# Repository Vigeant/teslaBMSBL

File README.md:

# teslaBMSBL

## Hardware

see eagle files to build the board hosting the teensy 3.2.

## dependencies

- TeensyView libs
  - <https://github.com/sparkfun/SparkFun_TeensyView_Arduino_Library/tree/master/examples>
- Snooze for lower power consumption
  - <https://github.com/duff2013/Snooze>

## Error codes on teensyView

| code | definition |
|:----:|------------|
| A | Modules Fault Loop |
| B | Battery Monitor Fault |
| C | BMS Serial communication Fault |
| D | BMS Cell Over Voltage Fault |
| E | BMS Cell Under Voltage Fault |
| F | BMS Over Temperature Fault |
| G | BMS Under Temperature Fault |
| H | BMS 12V Battery Over Voltage Fault |
| I | BMS 12V Battery Under Voltage Fault |
| J | BMS Water Sensor 1 Fault |
| K | BMS Water Sensor 2 Fault |
| L | Incorrect modules count |

## Connection to USB serial console

Serial Line: COMX (X typically = 7)
Speed: 115200

## controller state machine

<!-- [State machine](https://online.visual-paradigm.com/w/pmcoivfe/diagrams.jsp#diagram:proj=0&id=3) -->

```mermaid
    stateDiagram-v2

    state "INIT

    outL_12V_bat_chrg_buffer = 1;
    outpwm_pump_buffer = 0;
    outL_evcc_on_buffer = 1;
    outH_fault_buffer = 0;" as INIT

    state "STANDBY

    balanceCells();
    outL_evcc_on_buffer = HIGH;
    outH_fault_buffer = chargerInhibit;
    outL_12V_bat_chrg_buffer = !dc2dcON_H;
    outpwm_pump_buffer = 0;" as STANDBY

    state "RUN

    outL_evcc_on_buffer = LOW;
    outH_fault_buffer = powerLimiter;
    outL_12V_bat_chrg_buffer = LOW;
    outpwm_pump_buffer = YES" as RUN

    state "PRE_CHARGE

    balanceCells();
    outL_evcc_on_buffer = LOW;
    outH_fault_buffer = chargerInhibit;
    outL_12V_bat_chrg_buffer = !dc2dcON_H;
    outpwm_pump_buffer = 0;
    msgStatusIns.bBMSStatusFlags = 0;" as PRE_CHARGE

    state "CHARGING

    balanceCells();
    outL_evcc_on_buffer = LOW;
    outH_fault_buffer = chargerInhibit;
    outL_12V_bat_chrg_buffer = LOW;
    outpwm_pump_buffer = YES;
    msgStatusIns.bBMSStatusFlags = 0;" as CHARGING

    state "TOP_BALANCING

    balanceCells();
    msgStatusIns.bBMSStatusFlags |= BMS_STATUS_CELL_BVC_FLAG;
    outL_evcc_on_buffer = LOW;
    outH_fault_buffer = chargerInhibit;
    outL_12V_bat_chrg_buffer = HIGH;
    outpwm_pump_buffer = YES;
    msgStatusIns.bBMSStatusFlags = BMS_STATUS_CELL_BVC_FLAG;" as TOP_BALANCING

    state "POST_CHARGE

    balanceCells();
    outL_evcc_on_buffer = HIGH;
    outH_fault_buffer = HIGH;
    outL_12V_bat_chrg_buffer = HIGH;
    outpwm_pump_buffer = YES;
    msgStatusIns.bBMSStatusFlags = BMS_STATUS_CELL_HVC_FLAG;" as POST_CHARGE

    [*] --> INIT

    INIT --> STANDBY

    STANDBY --> RUN : INH_RUN == HIGH
    STANDBY --> PRE_CHARGE : getHighCellVolt < charger_cycle_v_setpoint && \ngetHighCellVolt < max_charge_v_setpoint && \nticks >= standbyTicks
    STANDBY --> CHARGING : INH_CHARGING == HIGH

    PRE_CHARGE --> STANDBY : INL_EVSE_DISC == LOW
    PRE_CHARGE --> CHARGING :INH_CHARGING == HIGH
    PRE_CHARGE --> STANDBY : ticks > 100

    CHARGING --> POST_CHARGE : ticks >= 5 && \nINL_EVSE_DISC == LOW || \nINH_CHARGING == LOW
    CHARGING --> TOP_BALANCING : getHighCellVolt >= top_balance_v_setpoint

    TOP_BALANCING --> POST_CHARGE : ticks >= 5 && \nINL_EVSE_DISC == LOW || \nINH_CHARGING == LOW

    POST_CHARGE --> STANDBY : ticks >= 50 && \nINH_CHARGING == LOW

    RUN --> STANDBY : INH_RUN == LOW

```

## todo

- [X] none

## particularities

Due to the 5s deepsleep mode in standby, it is hard to connect the serial console. To make it easier, either connect within 10 minutes of a reset or place the bms in run mode and connect.
Due to the deepsleep mode, it is impossible to simply reprogram the teensy following the first sleep. To facilitate reprogramming, the board will not sleep for 10 minutes following a reset.
The teensyview cannot be shut down as it is connected straight to the VDD pins.

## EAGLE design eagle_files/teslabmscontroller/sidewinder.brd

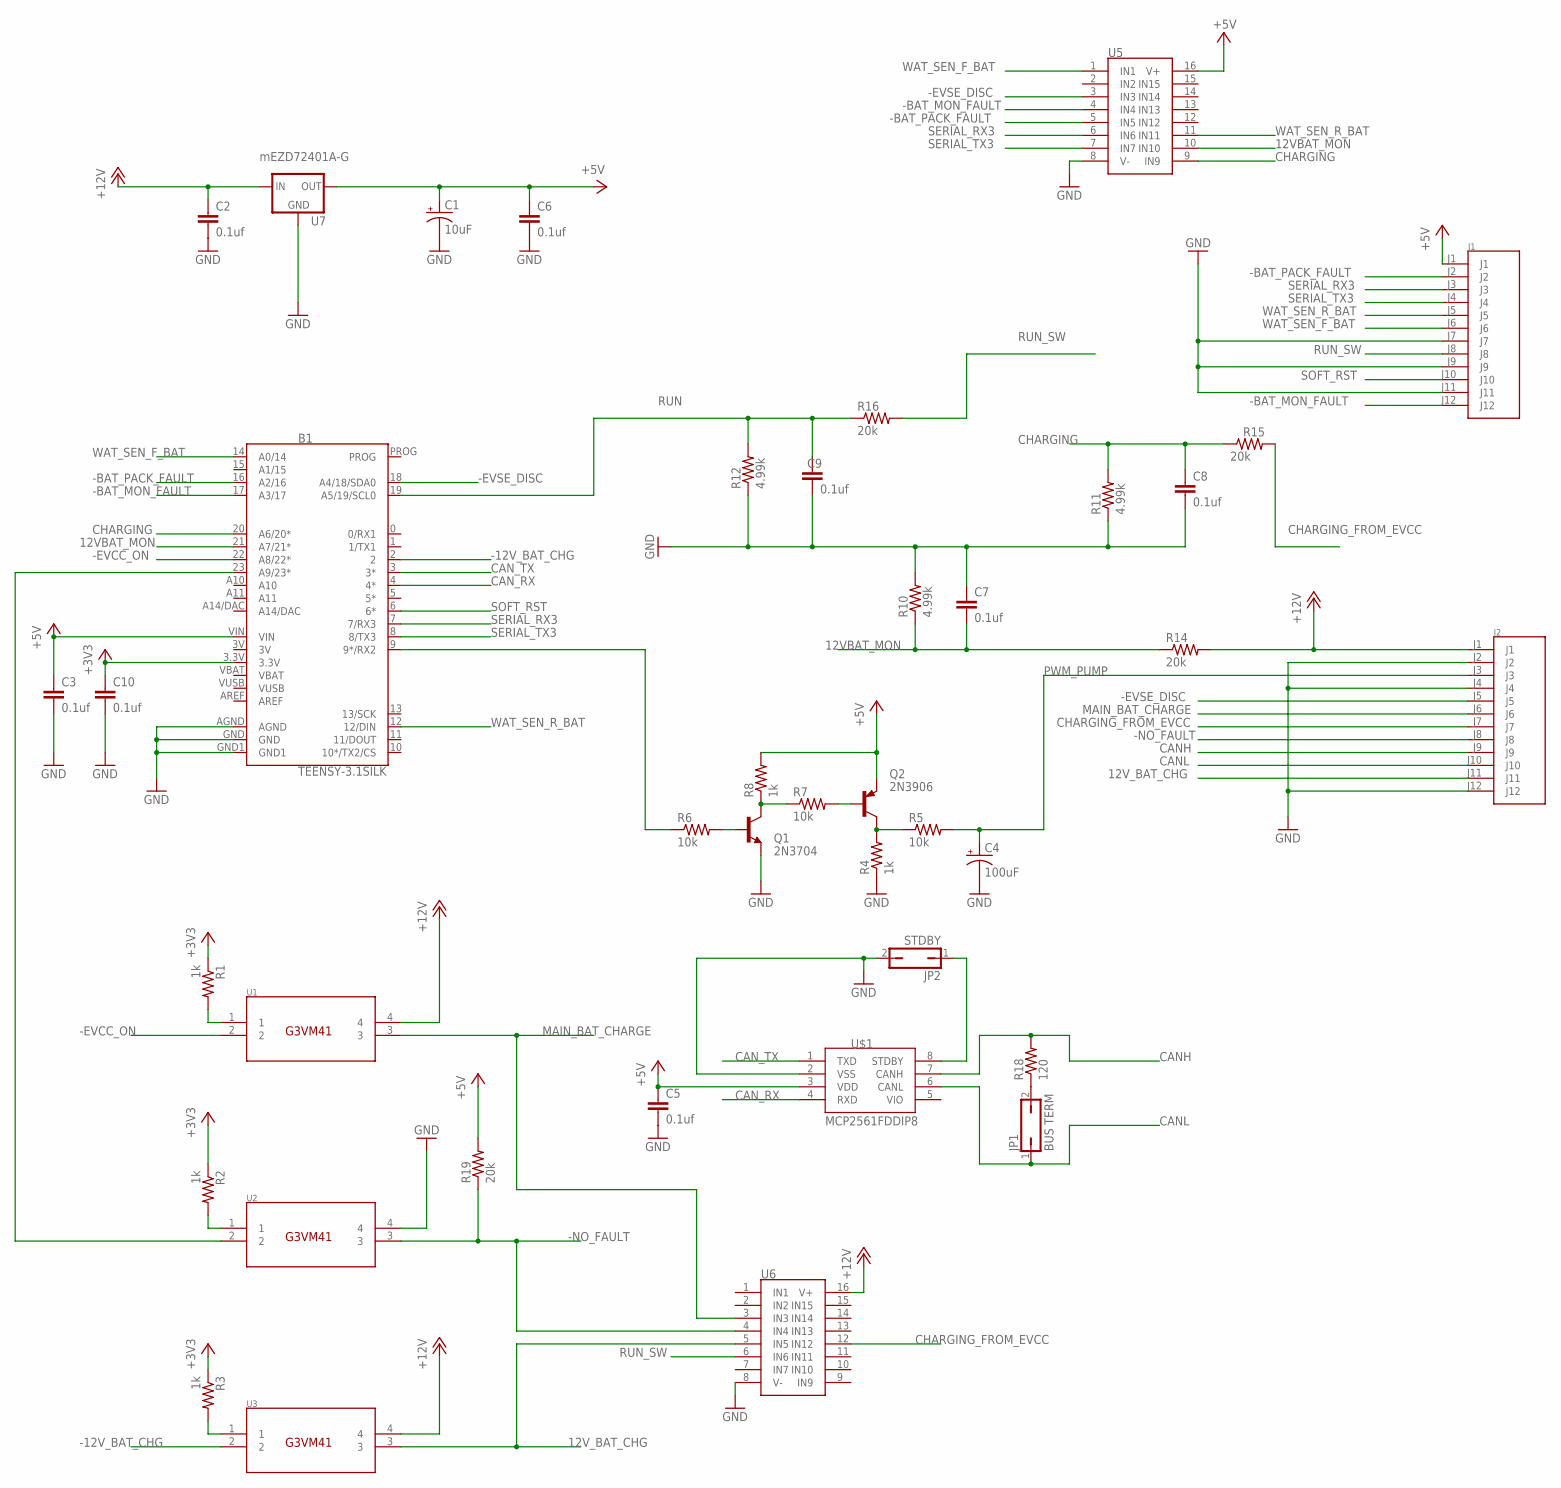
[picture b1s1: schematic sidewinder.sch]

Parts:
B1: TEENSY-3.1SILK; TEENSY-3.1
C1: 10uF; CPOL-RADIAL-2.5MM-5MM
C2, C3, C5, C6, C7, C8, C9, C10: 0.1uf; C2.5-2
C4: 100uF; CPOL-RADIAL-2.5MM-6.5MM
J1, J2: TERMINAL12
JP1: BUS TERM; JP1
JP2: STDBY; JP1
Q1: 2N3704; TO92
Q2: 2N3906; TO92
R1, R2, R3, R4, R8: 1k; 0207/10
R5, R6, R7: 10k; 0207/10
R10, R11, R12: 4.99k; 0207/10
R14, R15, R16, R19: 20k; 0207/10
R18: 120; 0207/10
U1, U2, U3: G3VM41
U5, U6: SP720APP; DIP16
U7: mEZD72401A-G; TO220-IGO
U$1: MCP2561FDDIP8; DIP787W45P254L949H533Q8B

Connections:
3V: B1.3V
12VBAT_MON: B1.21 (A7/21*), C7.2, R10.1, R14.1, U5.10 (IN10)
12V_BAT_CHG: J2.J11, U3.3, U6.5 (IN5)
+3V3: B1.3.3V, C10.1, R1.1, R2.1, R3.1
+5V: B1.VIN, C1.1 (+), C3.1, C5.1, C6.1, J1.J1, Q2.3 (E), R8.2, R19.2, U5.16 (V+), U7.OUT, U$1.3 (VDD)
+12V: C2.1, J2.J1, R14.2, U1.4, U3.4, U6.16 (V+), U7.IN
-12V_BAT_CHG: B1.2, U3.2
-BAT_MON_FAULT: B1.17 (A3/17), J1.J12, U5.4 (IN4)
-BAT_PACK_FAULT: B1.16 (A2/16), J1.J2, U5.5 (IN5)
-EVCC_ON: B1.22 (A8/22*), U1.2
-EVSE_DISC: B1.18 (A4/18/SDA0), J2.J5, U5.3 (IN3)
-NO_FAULT: J2.J8, R19.1, U2.3, U6.4 (IN4)
CANH: J2.J9, R18.2, U$1.7 (CANH)
CANL: J2.J10, JP1.1, U$1.6 (CANL)
CAN_RX: B1.4 (4*), U$1.4 (RXD)
CAN_TX: B1.3 (3*), U$1.1 (TXD)
CHARGING: B1.20 (A6/20*), C8.1, R11.2, R15.1, U5.9 (IN9)
CHARGING_FROM_EVCC: J2.J7, R15.2, U6.12 (IN12)
GND: B1.AGND, B1.GND, B1.GND1, C1.2 (-), C2.2, C3.2, C4.2 (-), C5.2, C6.2, C7.1, C8.2, C9.2, C10.2, J1.J7, J1.J9, J1.J11, J2.J2, J2.J4, J2.J12, JP2.2, Q1.3 (E), R4.1, R10.2, R11.1, R12.1, U2.4, U5.8 (V-), U6.8 (V-), U7.GND, U$1.2 (VSS)
MAIN_BAT_CHARGE: J2.J6, U1.3, U6.3 (IN3)
unnamed: B1.23 (A9/23*), U2.2
unnamed: B1.9 (9*/RX2), R6.1
unnamed: Q1.1 (B), R6.2
unnamed: Q1.2 (C), R7.1, R8.1
unnamed: Q2.2 (B), R7.2
unnamed: R1.2, U1.1
unnamed: R2.2, U2.1
unnamed: R3.2, U3.1
unnamed: Q2.1 (C), R4.2, R5.1
unnamed: JP2.1, U$1.8 (STDBY)
unnamed: JP1.2, R18.1
PWM_PUMP: C4.1 (+), J2.J3, R5.2
RUN: B1.19 (A5/19/SCL0), C9.1, R12.2, R16.1
RUN_SW: J1.J8, R16.2, U6.6 (IN6)
SERIAL_RX3: B1.7 (7/RX3), J1.J3, U5.6 (IN6)
SERIAL_TX3: B1.8 (8/TX3), J1.J4, U5.7 (IN7)
SOFT_RST: B1.6 (6*), J1.J10
VBAT: B1.VBAT
VUSB: B1.VUSB
WAT_SEN_F_BAT: B1.14 (A0/14), J1.J6, U5.1 (IN1)
WAT_SEN_R_BAT: B1.12 (12/DIN), J1.J5, U5.11 (IN11)

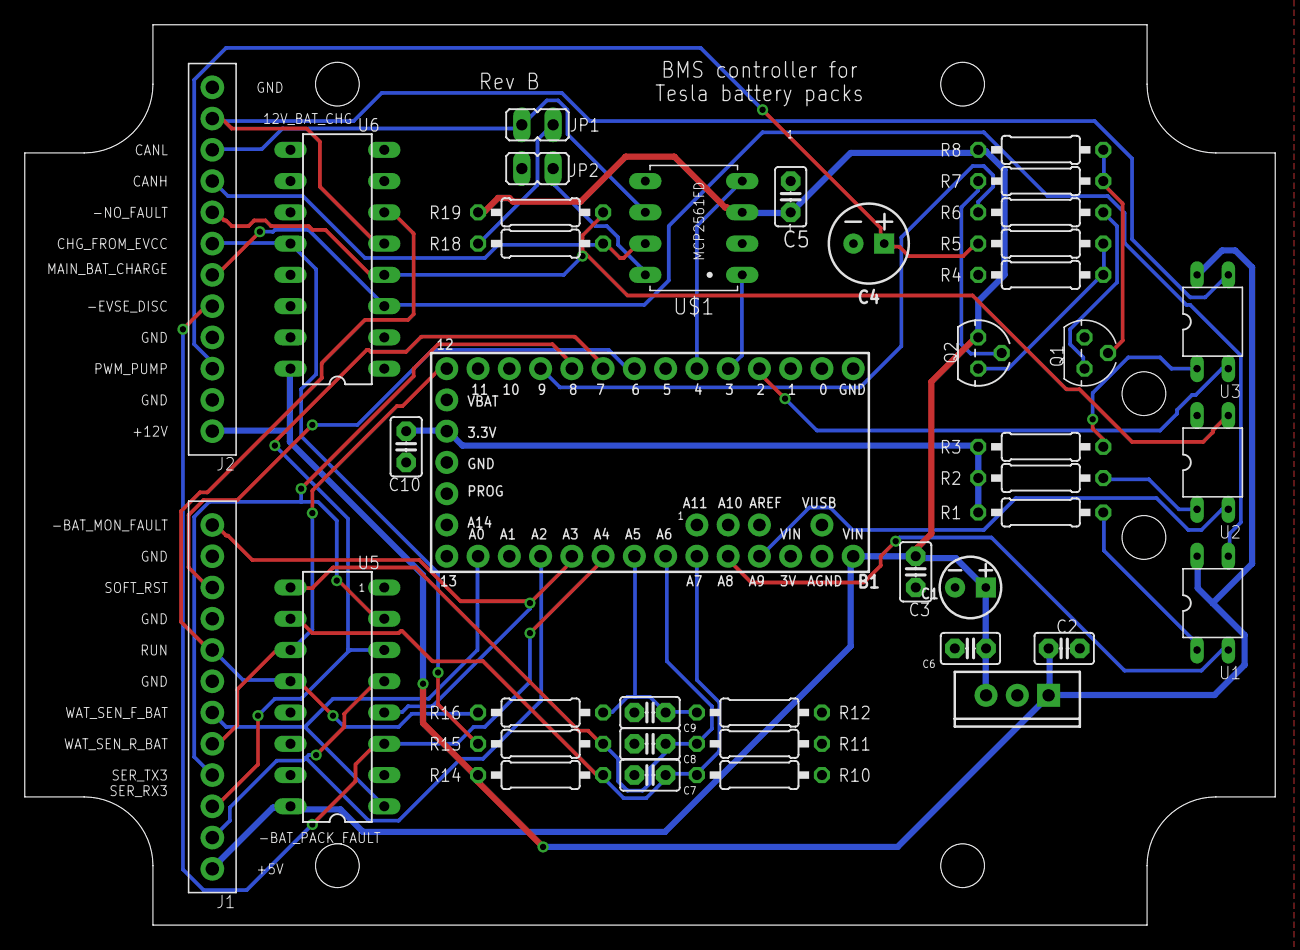
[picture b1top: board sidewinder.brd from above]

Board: 2 copper layers, 101.6 x 73.2 mm, 40 parts (0 on the bottom side), 38 nets.

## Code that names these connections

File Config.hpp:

#pragma once

#include <Arduino.h>
#include <EEPROM.h>
#include <list>

//enable testing mode that simply cycles through all states instead of triggers
//#define STATECYCLING 1
#define TESTING_MODE 0

///////////////////////////////////
// Teensy pin configuration      //
///////////////////////////////////
//side 1
//#define SERIAL1_RX          0
//#define SERIAL1_TX          1
#define OUTL_12V_BAT_CHRG 2  //Drive low to turn the DC2DC converter to charge the 12V battery
#define CAN_TX 3
#define CAN_RX 4
#define OLED_PIN_DC 5
#define INL_SOFT_RST 6  // soft reset of the teensy
#define SERIAL3_RX 7    // from Tesla BMS
#define SERIAL3_TX 8    // to Tesla BMS
#define OUTPWM_PUMP 9   // PWM to coolant pump
#define OLED_PIN_CS 10
#define OLED_PIN_MOSI 11
#define INL_WATER_SENS1 12  // battery enclosure water sensor 1

//side 2
#define OLED_PIN_SCK 13     //LED
#define INL_WATER_SENS2 14  // battery enclosure water sensor 2
#define OLED_PIN_RESET 15
#define INL_BAT_PACK_FAULT 16  //Tesla Battery pack fault.
#define INL_BAT_MON_FAULT 17   //Battery Monitor Fault.
#define INL_EVSE_DISC 18       //Electric Vehicle Supply Equipment Disconnected (from EVCC). (set Out2)
#define INH_RUN 19             //RUN signal from power relay with voltage divider from 12V to 3.3V.
#define INH_CHARGING 20        //CHARGING signal from EVCC. (Set Out1 to charging switched 12V)
#define INA_12V_BAT A7         //PIN21 12v battery monitor. Analog input with 12V to 3.3V voltage divider.
#define OUTL_EVCC_ON 22        //drive low to power on EVCC. Cycling this signal will force a new charge cycle.
#define OUTH_FAULT 23          //drive low to signal no fault to EVCC. Required for EVCC to charge.

//top side
//short P and G to reset board into program mode using push button

//Set to the proper port for your USB connection - SerialUSB on Due (Native) or Serial for Due (Programming) or Teensy
#define SERIALCONSOLE Serial

/*
   State machine
*/
// Loop periods for the state machine of the controller
#define LOOP_PERIOD_ACTIVE_MS 200

#define EEPROM_VERSION 6

#define CPU_RESTART_ADDR (uint32_t *)0xE000ED0C
#define CPU_RESTART_VAL 0x5FA0004
#define CPU_RESTART (*CPU_RESTART_ADDR = CPU_RESTART_VAL);

class Param {
public:
  Param(const char* paramName, bool editable, const char* description)
    : paramName(paramName),
      editable(editable),
      description(description) {
    ;
  }
  const char* paramName;
  virtual void prettyPrint();
  virtual int32_t setVal(const char* valStr);
  virtual uint16_t getSize();
  virtual void resetDefault();
  virtual uint32_t saveToEEPROM(uint32_t address);
  virtual uint32_t loadFromEEPROM(uint32_t address);
protected:
  bool editable = true;
  const char* description;
};

template<class C> class ParamImpl : public Param {
public:
  ParamImpl(const char* paramName, bool editable, C value, C valueDefault, C valueMin, C valueMax, const char* description)
    : Param(paramName, editable, description),
      value(value),
      valueDefault(valueDefault),
      valueMin(valueMin),
      valueMax(valueMax) {
    ;
  }

  void prettyPrint();
  int32_t setVal(const char*);

  C getVal() {
    return value;
  }

  void resetDefault() {
    value = valueDefault;
  }

  uint16_t getSize();
  bool valueMatchDefault() {
    return (value == valueDefault);
  }

  uint32_t saveToEEPROM(uint32_t address) {
    EEPROM.put(address, value);
    return sizeof(C);
  }

  uint32_t loadFromEEPROM(uint32_t address) {
    EEPROM.get(address, value);
    return sizeof(C);
  }

private:
  C value;
  C valueDefault;
  C valueMin;
  C valueMax;
};

class Settings {
public:
  void printSettings();
  Settings();
  Param* getParam(const char* name);
  uint16_t size();
  void reloadDefaultSettings();
  void saveAllSettingsToEEPROM(uint32_t address);
  void loadAllSettingsFromEEPROM(uint32_t address);

  ParamImpl<uint32_t> magic_bytes;
  ParamImpl<uint32_t> eeprom_version;
  ParamImpl<uint32_t> canbus_speed;
  ParamImpl<uint32_t> canbus_to_EVCC;
  ParamImpl<float> over_v_setpoint;
  ParamImpl<float> under_v_setpoint;
  ParamImpl<float> max_charge_v_setpoint;
  ParamImpl<float> charger_cycle_v_setpoint;
  ParamImpl<float> top_balance_v_setpoint;
  ParamImpl<float> warn_cell_v_offset;
  ParamImpl<float> floor_duty_coolant_pump;
  ParamImpl<float> cooling_lowt_setpoint;
  ParamImpl<float> cooling_hight_setpoint;
  ParamImpl<float> over_t_setpoint;
  ParamImpl<float> under_t_setpoint;
  ParamImpl<float> warn_t_offset;
  ParamImpl<float> precision_balance_v_setpoint;
  ParamImpl<float> precision_balance_cell_v_offset;
  ParamImpl<float> rough_balance_v_setpoint;
  ParamImpl<float> rough_balance_cell_v_offset;
  ParamImpl<float> dc2dc_cycle_v_setpoint;
  ParamImpl<uint32_t> dc2dc_cycle_time_s;
  ParamImpl<float> bat12v_over_v_setpoint;
  ParamImpl<float> bat12v_under_v_setpoint;
  ParamImpl<float> bat12v_scaling_divisor;
  ParamImpl<uint32_t> fault_debounce_count;
  ParamImpl<uint32_t> module_count;
  ParamImpl<uint32_t> oled_cycle_time;
  ParamImpl<uint32_t> time_before_first_sleep;

private:
  std::list<Param*> parameters;
};

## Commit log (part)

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2019-03-20 initial push
    Transitioned to the big loop design with a schedule.
2019-03-21 adding doxygen
2019-03-22 generated doxygen documentation
2019-03-22 added print summaries to the console
2019-03-22 tweaked the init state
2019-03-22 added colant pump pwm
2019-03-23 updated readme todo
2019-03-25 worked on state machine
2019-03-25 finished state machine
2019-03-25 cleaned config.h
2019-03-27 completed battery summary
2019-03-27 optimized controller
2019-03-27 fixes
2019-03-27 improved pack summary
2019-03-27 added 12V bat stats
2019-03-27 fixed bug in controller
2019-04-28 added hysterisy for faults
    after witnessing some fault glitches, we added hysteresy that requires the fault to be present for three ticks for it to be considered.
    Fixed coolant pump scaling issue,
    Added some more balancing functionality. More thaught required.
2019-05-04 safer behavior
    This will keep the dc2dc on while it waits for the charger to turn on.
2019-05-05 fixed console sometimes dropping a character
2019-05-06 added controller fault printout
2019-05-17 showing current vdmax on oled
2019-05-26 implemented the two water sensor lines
2019-05-26 fixed init of water sensor pins
2019-07-06 adjusted 12v divisor
2019-07-07 ADJUSTED SCALING
2019-07-09 major state machine change
    Modified the state machine to reflect the actual behavior of the EVCC module.
2019-07-10 deepSleep mode added
2019-07-11 Update Controller.cpp
    prevents to sleep for 1 minute in standby to allow for reprogramming following a reset.
2019-07-12 updated doc
2019-07-12 started a manual
2019-10-27 fixed sleeping
    sleep was preventing balancing
2019-10-29 Update Controller.cpp
    flipped the polarity of the PWM controlling the pump
2019-11-09 Revert "Update Controller.cpp"
    This reverts commit 1ec6cf16614d8a641a1f77b5105418e0ae55e478.
2019-12-27 added PWM test program
2020-03-27 added eagle files
2020-04-27 fixed wrong form factor for chip
2020-06-14 fixed RUN
    RUN signal was absent from connector
    flipped whole board so silk alligns with OLED
    fixed routing issu of can chip
2020-06-16 bug fixes
2020-06-16 run and charging to zener
2020-06-16 adjusted 12Vto5V deviders
    changed 2 resistors from 10k to 15k after we fried a board...
2020-07-02 added EVCC_config.txt
    added the config of the EVCC controller
2020-07-02 added standby to charging transition in controller.cpp
    updated the documentation with the new state machine.
    INL_CHARGING changed to INH_CHARGING in the diagram.
2021-08-24 Update Controller.cpp
    added logic to the charging state to stop the charger when the max charge v setpoint is reached.
    Also added a timeout of 100 ticks to the pre-charge state where if the charger did not start it will go back to standby.
2021-08-31 Update Controller.cpp
    added some comments in the state machine to capture some important decisions regarding allowing the EVCC to stay on and allowing to charge when in run mode.
2021-09-06 tweaks
    adjusted 12V scaling
    limit VBat to 1 digit on the OLED
2021-09-06 state machine tweaks
    adjusted the charcher V setpoint to 4.0V from 3.9V but now check the highest cell instead of the lowest cell. This prevents endless cycling of the charger and when the highest cell is below a voltage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
2022-03-22 Update Controller.cpp
    adjusted pre-charge delay form 3 seconds to 10 seconds.
2022-06-18 adjusted config thresholds
2022-06-18 Update CONFIG.h
    adjusted fine balancing to 0.02v
2022-06-18 UI modifications
    printing outputs in console formats to help debugging.
2022-06-19 evcc integration
    debounced the inh_charging.
2022-07-29 config tweaks
    adjusted some threshold t help balance tighter.
2022-07-31 updated BMS board
    fixed can bus chip and changed 5v regulator to a switching to avoid heat.
2022-08-06 added trickle charge state
    the final charging requires the dc2dc to be turned off to be able to properly measure the the current drop. the trickle charging state is the same as the charging state but turns off the dc2dc and is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
2022-08-08 reworked fault logic
    refactored faults as a struct array and removed a lot of duplicated code.
2022-08-25 Implemented real CLI
    Preparing the CLI to accomodate live configuration of the board through CLI.
2022-09-10 param rework
    Building the scafolding for the eeprom config and CLI configuration of all settings.
2022-09-11 major configuration rework
    config is now captured in the Settings class.
    - automatically works with the console
    - TODO console set param feature (use of specialized members)
    - TODO serialization of settings in EEPROM and logic to load smartly.
2022-09-11 added set param function
    - Added new cli command to set a parameter to a value (non persistent for now).
    - Removed the use of an array of objects to a list for commands.
2022-09-17 config parameters rework
    Added functionality to set config parameters which saves them to the eeprom automatically. When the BMS loads, it loads the config from the EEPROM automatically and verifies the magic bytes and the v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
2022-09-20 code cleanup
    - converted faults array of struct to list of Fault classes.
    - added a new config param for adjusting the fault debounce counter.
    - code cleanup and refactoring in general.
2022-10-05 added module count error
2022-10-05 added RTC timestamps
2022-10-07 added time command
    the time command in the cli allows setting the time and date.
2022-10-07 fixed oled cycling
    fixed oled that would cycle slowly when in deepsleep mode.
    - added a config setting for adjusting how fast the oled cycles.
2022-10-16 fixed typos in config description
2022-10-16 added net setting for first sleep
2022-12-03 Update Controller.cpp
    removed the battery monitor fault from the charge fault to allow charging when the battery is very low and bat mon is faulted.
2022-12-04 Update Cons.hpp
    Update the RTC when changing the system time.
2022-12-05 added CAN bus functionality
    Added CAN bus to EVCC functionality.
    This allows telling the EVCC to scale down current for top balancing mode.
    This also allows telling the EVCC more precise errors such as over voltage, under voltage and over temp.
2023-08-26 fixed CAN
    Fixed can bus
    fixed bug on PCB where run input was connected to both 5v and 12v chips.
2023-08-26 timestamps rework and can fix
    Afficher l’heure du last reset plutôt que le temps depuis, maintenant qu’on a un RTC 😉
    Afficher un format simplifié (moins techno) de date and time genre « Aug 8, 2023 16:41:00 »
    Afficher le pack voltage (total) le plus bas (min) et le plus haut (max) détecté, ainsi que les températures minimales et maximale détectées, avec la commande « 1 », idéalement avec le time stamp 😉
    Changer le terme « trickle charge » pour « top balancing » ou « fine balancing » pour le distinguer du « rough balancing »
2023-08-26 Update Controller.cpp
    fixed a possible charging initiation problem where EVCC might take a while to report its charging.
2023-09-01 cooling pump duty enabled
    Re-enabled the cooling pump duty calculation.
2023-09-03 printing fixes
2023-09-13 removed al sleeping logic
    trying to hunt the sporadic reset of the teensy 3.2.
2024-03-29 Update README.md
    created the mermaid state diagram for the controller

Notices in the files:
parts and their libraries:
SparkFun-Boards: Licensing: Creative Commons ShareAlike 4.0 International - https://creativecommons.org/licenses/by-sa/4.0
